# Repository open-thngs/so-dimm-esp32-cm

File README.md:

# SO-DIMM-ESP32-S2-CM

This is a ESP32-S2 based Compute Module to replace the Raspberry Pi's Compute Modules CM2 and CM3. This module is footprint compatible to the Raspberry Pi CM (SO-DIMM-DDR2). The ESP32-S2 brings USB, I2C and SPI.

Because the ESP32 is not running a Linux OS this module can not replace any CM in any project due to its limitations but it might helps others to reduce cost and resources needed to run the project. The ESP32-S2 consumes only 1/3 of the power the CM does. The ESP can also bring WiFi to your project if needed.

The Module also contains 2x GPIO-Expander which are used to be compatible with any GPIO of the Raspberry Pi Compute Module which gives you 48 GPIOs to be used in total.

Features:
- 2x I2C
- 2x SPI
- 1x UART
- USB

## OSHW Certified

[OSHW] DE000133 | Certified open source hardware | oshwa.org/cert

[https://certification.oshwa.org/de000133.html](https://certification.oshwa.org/de000133.html)

## GPIO Reference

GPIO Expander references E1_IOX_Y = < Expander >_< Bank >_< GPIO >
Example: E1_IO0_2 is the GPIO 2 of the Bank 0 in GPIO Expander 1. GPIO count starts at 0.

GPIO Expander E1 has address 0x20
GPIO Expander E2 has address 0x21

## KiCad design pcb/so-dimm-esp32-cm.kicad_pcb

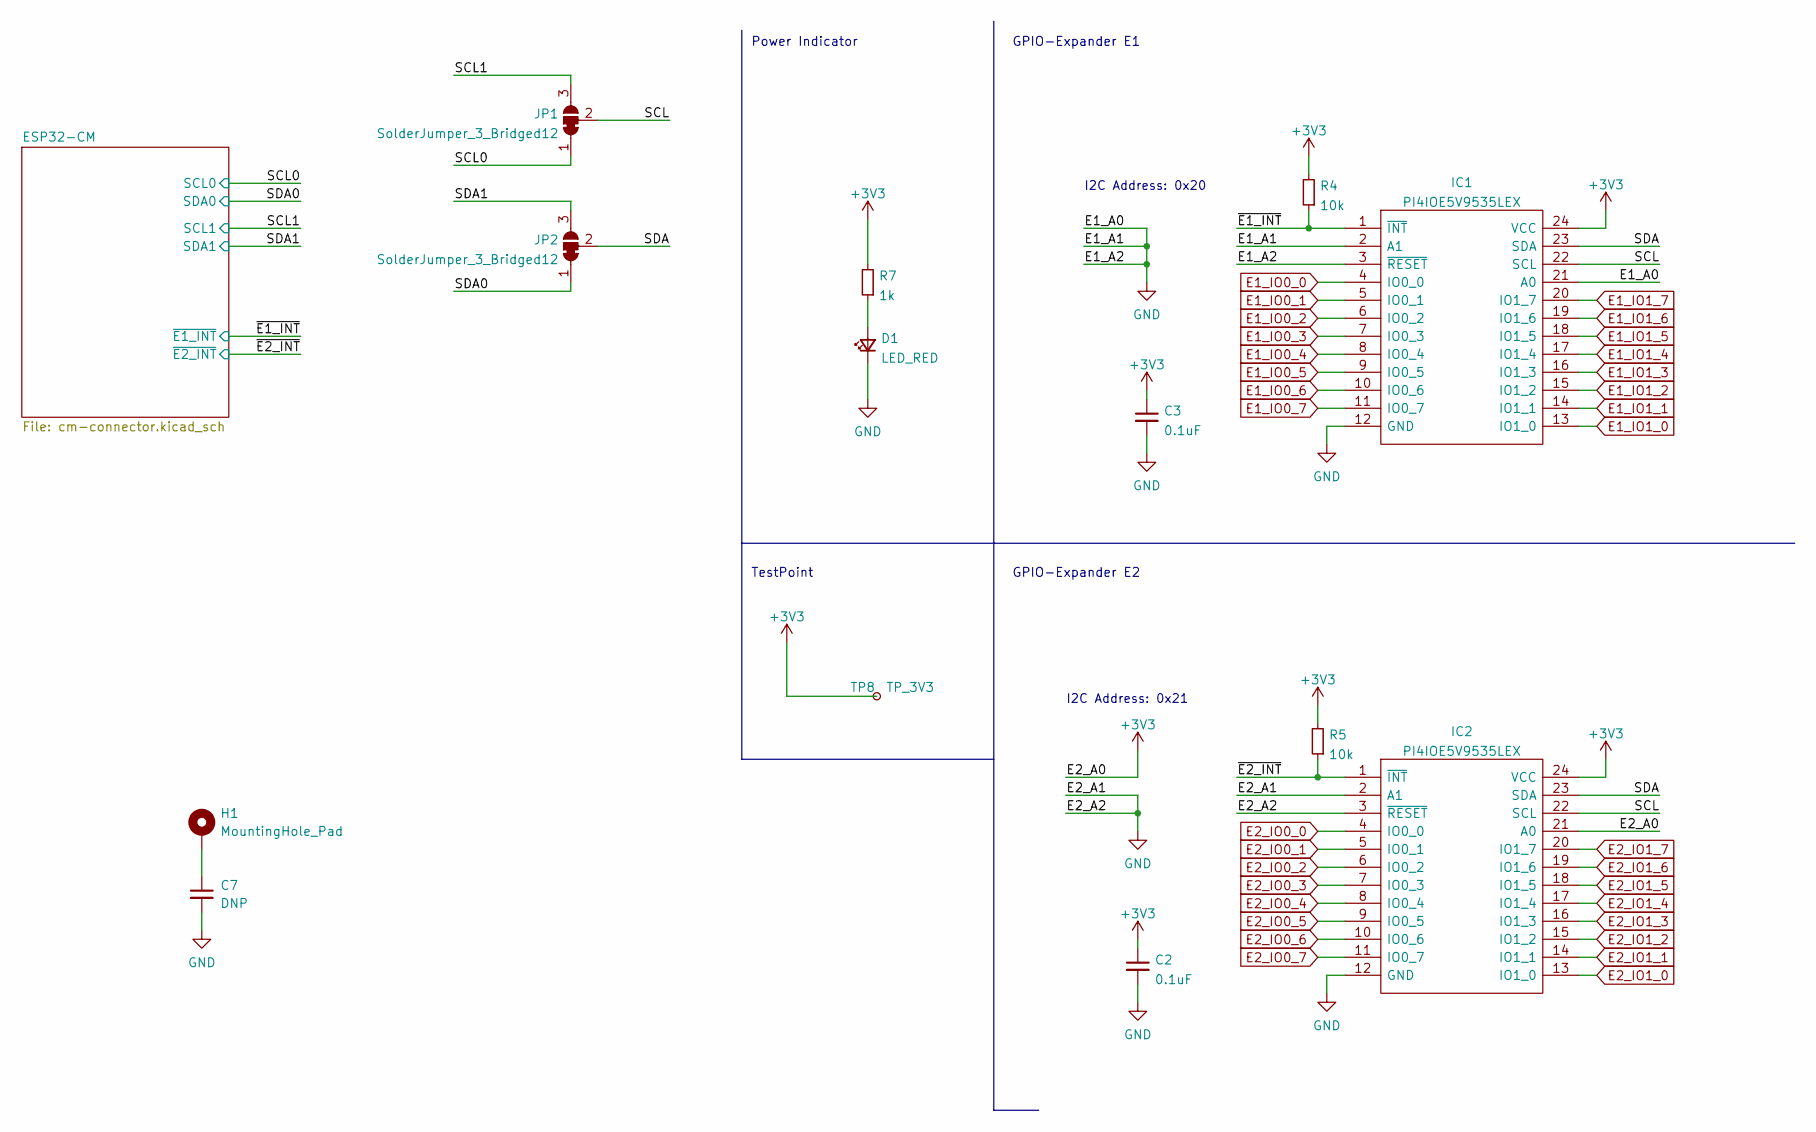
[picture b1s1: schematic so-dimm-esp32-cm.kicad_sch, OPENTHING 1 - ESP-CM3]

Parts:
C2, C3: 0.1uF; C_0603_1608Metric
C7: DNP; C_0603_1608Metric
D1: LED_RED; LED_0603_1608Metric
H1: MountingHole_Pad; MountingHole_2.7mm_Pad_Via
IC1, IC2: PI4IOE5V9535LEX; SOP65P640X120-24N; Manufacturer_Part_Number PI4IOE5V9535LEX; Mouser Part Number 729-PI4IOE5V9535LEX
JP1, JP2: SolderJumper_3_Bridged12; SolderJumper-3_P1.3mm_Bridged12_RoundedPad1.0x1.5mm
R4, R5: 10k; R_0603_1608Metric
R7: 1k; R_0603_1608Metric
TP8: TP_3V3; TestPoint_Pad_D1.0mm

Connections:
+3V3: C2.1, C3.1, IC1.24 (VCC), IC2.21 (A0), IC2.24 (VCC), R4.2, R5.2, R7.2, TP8.1; also elsewhere on the board
/SCL: IC1.22 (SCL), IC2.22 (SCL), JP1.2 (C)
/SCL0: JP1.1 (A); also elsewhere on the board
/SCL1: JP1.3 (B); also elsewhere on the board
/SDA: IC1.23 (SDA), IC2.23 (SDA), JP2.2 (C)
/SDA0: JP2.1 (A); also elsewhere on the board
/SDA1: JP2.3 (B); also elsewhere on the board
/~E1_INT: IC1.1 (~INT), R4.1; also elsewhere on the board
/~E2_INT: IC2.1 (~INT), R5.1; also elsewhere on the board
E1_IO0_0: IC1.4 (IO0_0); also elsewhere on the board
E1_IO0_1: IC1.5 (IO0_1); also elsewhere on the board
E1_IO0_2: IC1.6 (IO0_2); also elsewhere on the board
E1_IO0_3: IC1.7 (IO0_3); also elsewhere on the board
E1_IO0_4: IC1.8 (IO0_4); also elsewhere on the board
E1_IO0_5: IC1.9 (IO0_5); also elsewhere on the board
E1_IO0_6: IC1.10 (IO0_6); also elsewhere on the board
E1_IO0_7: IC1.11 (IO0_7); also elsewhere on the board
E1_IO1_0: IC1.13 (IO1_0); also elsewhere on the board
E1_IO1_1: IC1.14 (IO1_1); also elsewhere on the board
E1_IO1_2: IC1.15 (IO1_2); also elsewhere on the board
E1_IO1_3: IC1.16 (IO1_3); also elsewhere on the board
E1_IO1_4: IC1.17 (IO1_4); also elsewhere on the board
E1_IO1_5: IC1.18 (IO1_5); also elsewhere on the board
E1_IO1_6: IC1.19 (IO1_6); also elsewhere on the board
E1_IO1_7: IC1.20 (IO1_7); also elsewhere on the board
E2_IO0_0: IC2.4 (IO0_0); also elsewhere on the board
E2_IO0_1: IC2.5 (IO0_1); also elsewhere on the board
E2_IO0_2: IC2.6 (IO0_2); also elsewhere on the board
E2_IO0_3: IC2.7 (IO0_3); also elsewhere on the board
E2_IO0_4: IC2.8 (IO0_4); also elsewhere on the board
E2_IO0_5: IC2.9 (IO0_5); also elsewhere on the board
E2_IO0_6: IC2.10 (IO0_6); also elsewhere on the board
E2_IO0_7: IC2.11 (IO0_7); also elsewhere on the board
E2_IO1_0: IC2.13 (IO1_0); also elsewhere on the board
E2_IO1_1: IC2.14 (IO1_1); also elsewhere on the board
E2_IO1_2: IC2.15 (IO1_2); also elsewhere on the board
E2_IO1_3: IC2.16 (IO1_3); also elsewhere on the board
E2_IO1_4: IC2.17 (IO1_4); also elsewhere on the board
E2_IO1_5: IC2.18 (IO1_5); also elsewhere on the board
E2_IO1_6: IC2.19 (IO1_6); also elsewhere on the board
E2_IO1_7: IC2.20 (IO1_7); also elsewhere on the board
GND: C2.2, C3.2, C7.2, D1.1 (K), IC1.2 (A1), IC1.3 (~RESET), IC1.12 (GND), IC1.21 (A0), IC2.2 (A1), IC2.3 (~RESET), IC2.12 (GND); also elsewhere on the board
unnamed: C7.1, H1.1
unnamed: D1.2 (A), R7.1

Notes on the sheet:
I2C Address: 0x20
GPIO-Expander E1
TestPoint
I2C Address: 0x21
Power Indicator
GPIO-Expander E2

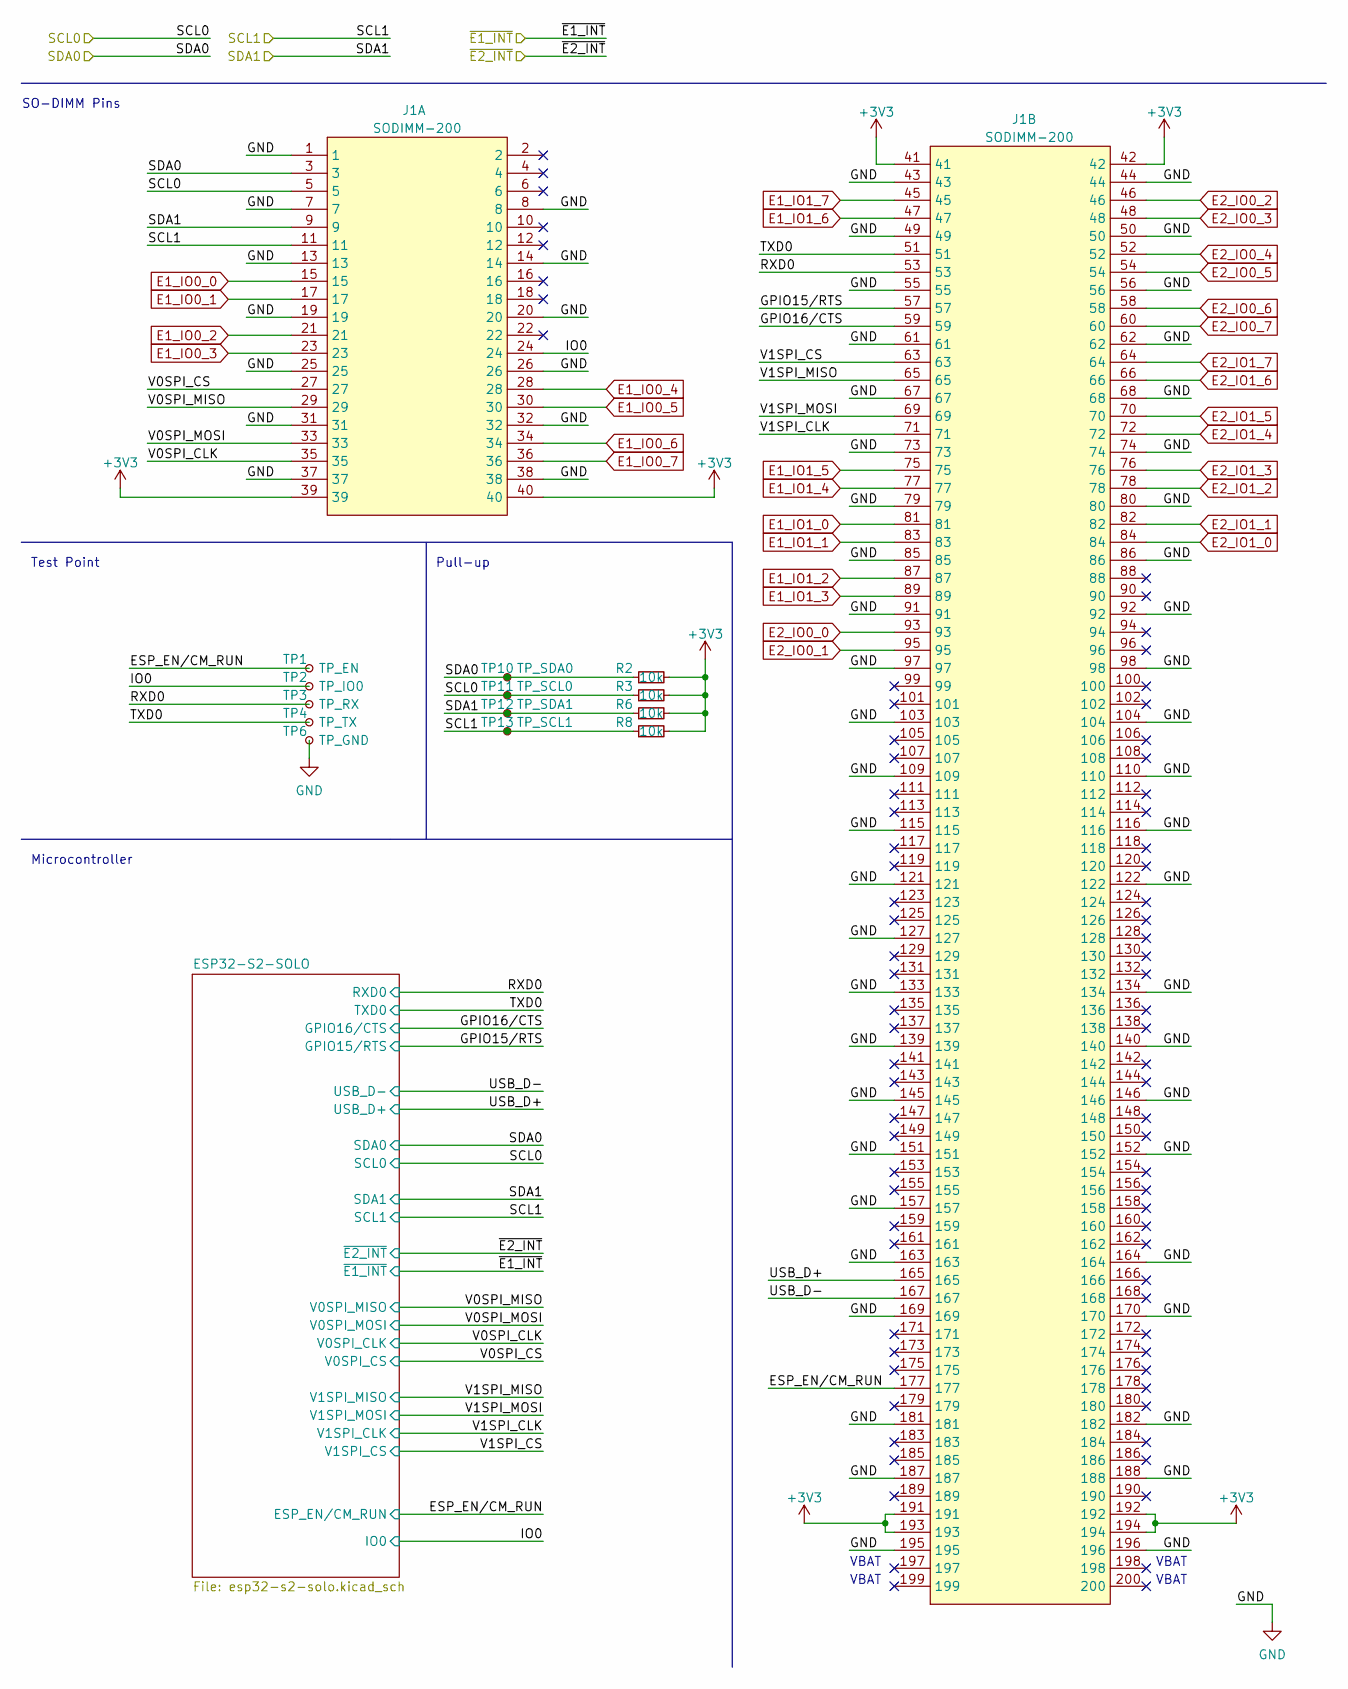
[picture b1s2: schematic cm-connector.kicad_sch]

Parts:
J1: SODIMM-200; SODIMM_DDR2_EDGE
R2, R3, R6, R8: 10k; R_0603_1608Metric
TP1: TP_EN; TestPoint_Pad_D1.0mm
TP2: TP_IO0; TestPoint_Pad_D1.0mm
TP3: TP_RX; TestPoint_Pad_D1.0mm
TP4: TP_TX; TestPoint_Pad_D1.0mm
TP6: TP_GND; TestPoint_Pad_D1.0mm
TP10: TP_SDA0; TestPoint_Pad_D1.0mm
TP11: TP_SCL0; TestPoint_Pad_D1.0mm
TP12: TP_SDA1; TestPoint_Pad_D1.0mm
TP13: TP_SCL1; TestPoint_Pad_D1.0mm

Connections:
+3V3: J1.39, J1.40, J1.41, J1.42, J1.191, J1.192, J1.193, J1.194, R2.2, R3.2, R6.2, R8.2; also elsewhere on the board
/ESP32-CM/ESP_EN/CM_RUN: J1.177, TP1.1; also elsewhere on the board
/ESP32-CM/GPIO15/RTS: J1.57; also elsewhere on the board
/ESP32-CM/GPIO16/CTS: J1.59; also elsewhere on the board
/ESP32-CM/IO0: J1.24, TP2.1; also elsewhere on the board
/ESP32-CM/RXD0: J1.53, TP3.1; also elsewhere on the board
/ESP32-CM/TXD0: J1.51, TP4.1; also elsewhere on the board
/ESP32-CM/USB_D+: J1.165; also elsewhere on the board
/ESP32-CM/USB_D-: J1.167; also elsewhere on the board
/ESP32-CM/V0SPI_CLK: J1.35; also elsewhere on the board
/ESP32-CM/V0SPI_CS: J1.27; also elsewhere on the board
/ESP32-CM/V0SPI_MISO: J1.29; also elsewhere on the board
/ESP32-CM/V0SPI_MOSI: J1.33; also elsewhere on the board
/ESP32-CM/V1SPI_CLK: J1.71; also elsewhere on the board
/ESP32-CM/V1SPI_CS: J1.63; also elsewhere on the board
/ESP32-CM/V1SPI_MISO: J1.65; also elsewhere on the board
/ESP32-CM/V1SPI_MOSI: J1.69; also elsewhere on the board
/SCL0: J1.5, R3.1, TP11.1; also elsewhere on the board
/SCL1: J1.11, R8.1, TP13.1; also elsewhere on the board
/SDA0: J1.3, R2.1, TP10.1; also elsewhere on the board
/SDA1: J1.9, R6.1, TP12.1; also elsewhere on the board
E1_IO0_0: J1.15; also elsewhere on the board
E1_IO0_1: J1.17; also elsewhere on the board
E1_IO0_2: J1.21; also elsewhere on the board
E1_IO0_3: J1.23; also elsewhere on the board
E1_IO0_4: J1.28; also elsewhere on the board
E1_IO0_5: J1.30; also elsewhere on the board
E1_IO0_6: J1.34; also elsewhere on the board
E1_IO0_7: J1.36; also elsewhere on the board
E1_IO1_0: J1.81; also elsewhere on the board
E1_IO1_1: J1.83; also elsewhere on the board
E1_IO1_2: J1.87; also elsewhere on the board
E1_IO1_3: J1.89; also elsewhere on the board
E1_IO1_4: J1.77; also elsewhere on the board
E1_IO1_5: J1.75; also elsewhere on the board
E1_IO1_6: J1.47; also elsewhere on the board
E1_IO1_7: J1.45; also elsewhere on the board
E2_IO0_0: J1.93; also elsewhere on the board
E2_IO0_1: J1.95; also elsewhere on the board
E2_IO0_2: J1.46; also elsewhere on the board
E2_IO0_3: J1.48; also elsewhere on the board
E2_IO0_4: J1.52; also elsewhere on the board
E2_IO0_5: J1.54; also elsewhere on the board
E2_IO0_6: J1.58; also elsewhere on the board
E2_IO0_7: J1.60; also elsewhere on the board
E2_IO1_0: J1.84; also elsewhere on the board
E2_IO1_1: J1.82; also elsewhere on the board
E2_IO1_2: J1.78; also elsewhere on the board
E2_IO1_3: J1.76; also elsewhere on the board
E2_IO1_4: J1.72; also elsewhere on the board
E2_IO1_5: J1.70; also elsewhere on the board
E2_IO1_6: J1.66; also elsewhere on the board
E2_IO1_7: J1.64; also elsewhere on the board
GND: J1.1, J1.7, J1.8, J1.13, J1.14, J1.19, J1.20, J1.25, J1.26, J1.31, J1.32, J1.37, J1.38, J1.43, J1.44, J1.49, J1.50, J1.55, J1.56, J1.61, J1.62, J1.67, J1.68, J1.73, J1.74, J1.79, J1.80, J1.85, J1.86, J1.91, J1.92, J1.97, J1.98, J1.103, J1.104, J1.109, J1.110, J1.115, J1.116, J1.121, J1.122, J1.127, J1.133, J1.134, J1.139, J1.140, J1.145, J1.146, J1.151, J1.152, J1.157, J1.163, J1.164, J1.169, J1.170, J1.181, J1.182, J1.187, J1.188, J1.195, J1.196, TP6.1; also elsewhere on the board

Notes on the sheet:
Microcontroller
SO-DIMM Pins
VBAT
Pull-up
Test Point

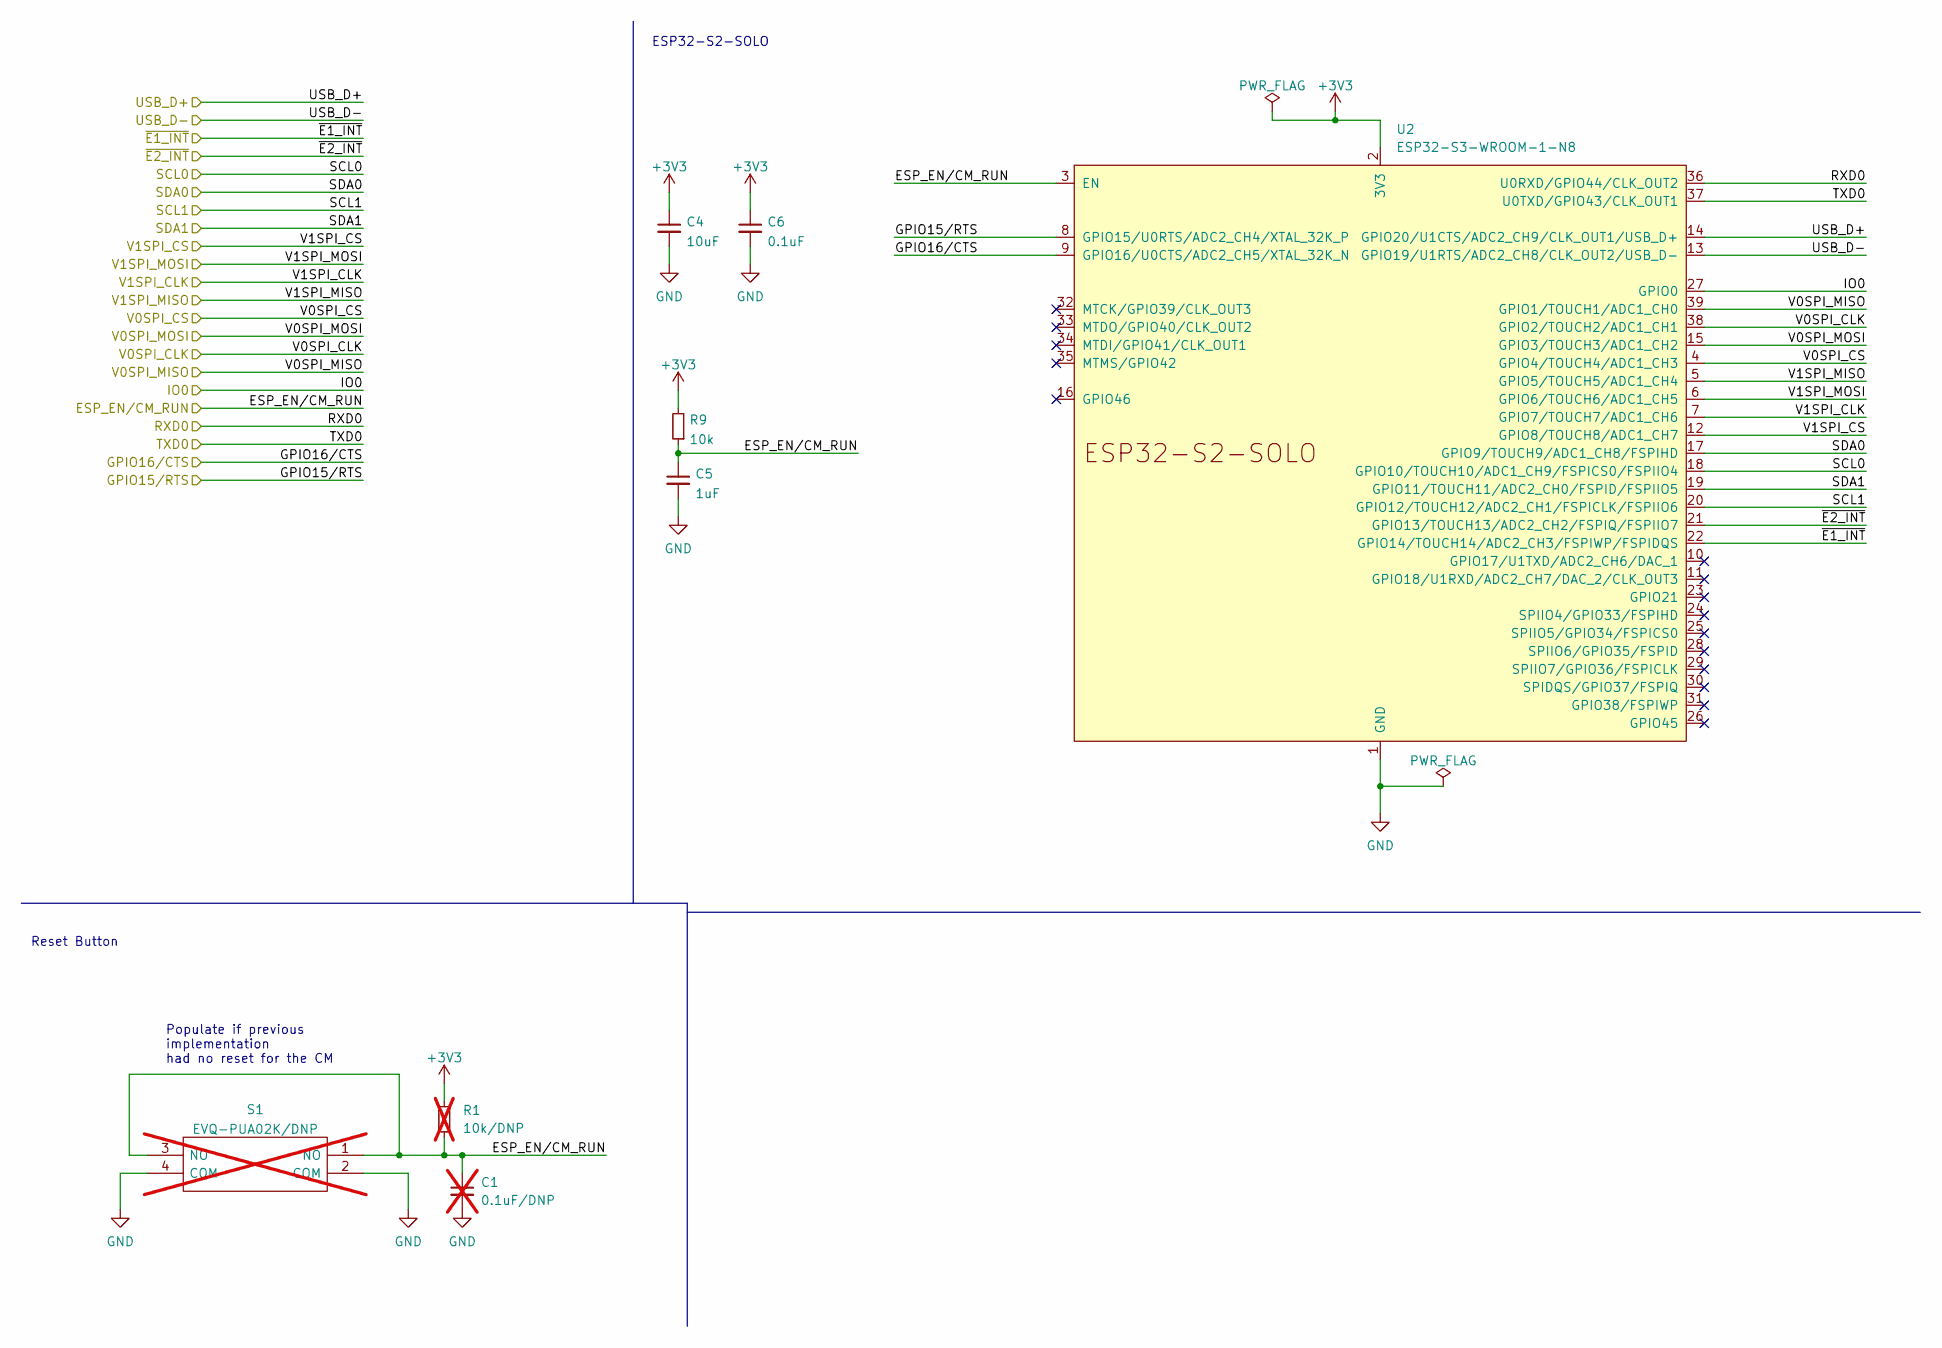
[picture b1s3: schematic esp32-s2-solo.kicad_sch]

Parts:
C1: 0.1uF/DNP; C_0603_1608Metric; not fitted
C4: 10uF; C_0603_1608Metric
C5: 1uF; C_0603_1608Metric
C6: 0.1uF; C_0603_1608Metric
R1: 10k/DNP; R_0603_1608Metric; not fitted
R9: 10k; R_0603_1608Metric
S1: EVQ-PUA02K/DNP; EVQPUA02K; Manufacturer_Part_Number EVQ-PUA02K; Mouser Part Number 667-EVQ-PUA02K; not fitted
U2: ESP32-S3-WROOM-1-N8; ESP32-S2-SOLO

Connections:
+3V3: C4.1, C6.1, R1.2, R9.2, U2.2 (3V3); also elsewhere on the board
/ESP32-CM/ESP_EN/CM_RUN: C1.1, C5.1, R1.1, R9.1, S1.1 (NO), S1.3 (NO), U2.3 (EN); also elsewhere on the board
/ESP32-CM/GPIO15/RTS: U2.8 (GPIO15/U0RTS/ADC2_CH4/XTAL_32K_P); also elsewhere on the board
/ESP32-CM/GPIO16/CTS: U2.9 (GPIO16/U0CTS/ADC2_CH5/XTAL_32K_N); also elsewhere on the board
/ESP32-CM/IO0: U2.27 (GPIO0); also elsewhere on the board
/ESP32-CM/RXD0: U2.36 (U0RXD/GPIO44/CLK_OUT2); also elsewhere on the board
/ESP32-CM/TXD0: U2.37 (U0TXD/GPIO43/CLK_OUT1); also elsewhere on the board
/ESP32-CM/USB_D+: U2.14 (GPIO20/U1CTS/ADC2_CH9/CLK_OUT1/USB_D+); also elsewhere on the board
/ESP32-CM/USB_D-: U2.13 (GPIO19/U1RTS/ADC2_CH8/CLK_OUT2/USB_D-); also elsewhere on the board
/ESP32-CM/V0SPI_CLK: U2.38 (GPIO2/TOUCH2/ADC1_CH1); also elsewhere on the board
/ESP32-CM/V0SPI_CS: U2.4 (GPIO4/TOUCH4/ADC1_CH3); also elsewhere on the board
/ESP32-CM/V0SPI_MISO: U2.39 (GPIO1/TOUCH1/ADC1_CH0); also elsewhere on the board
/ESP32-CM/V0SPI_MOSI: U2.15 (GPIO3/TOUCH3/ADC1_CH2); also elsewhere on the board
/ESP32-CM/V1SPI_CLK: U2.7 (GPIO7/TOUCH7/ADC1_CH6); also elsewhere on the board
/ESP32-CM/V1SPI_CS: U2.12 (GPIO8/TOUCH8/ADC1_CH7); also elsewhere on the board
/ESP32-CM/V1SPI_MISO: U2.5 (GPIO5/TOUCH5/ADC1_CH4); also elsewhere on the board
/ESP32-CM/V1SPI_MOSI: U2.6 (GPIO6/TOUCH6/ADC1_CH5); also elsewhere on the board
/SCL0: U2.18 (GPIO10/TOUCH10/ADC1_CH9/FSPICS0/FSPIIO4); also elsewhere on the board
/SCL1: U2.20 (GPIO12/TOUCH12/ADC2_CH1/FSPICLK/FSPIIO6); also elsewhere on the board
/SDA0: U2.17 (GPIO9/TOUCH9/ADC1_CH8/FSPIHD); also elsewhere on the board
/SDA1: U2.19 (GPIO11/TOUCH11/ADC2_CH0/FSPID/FSPIIO5); also elsewhere on the board
/~E1_INT: U2.22 (GPIO14/TOUCH14/ADC2_CH3/FSPIWP/FSPIDQS); also elsewhere on the board
/~E2_INT: U2.21 (GPIO13/TOUCH13/ADC2_CH2/FSPIQ/FSPIIO7); also elsewhere on the board
GND: C1.2, C4.2, C5.2, C6.2, S1.2 (COM), S1.4 (COM), U2.1 (GND), U2.40 (GND), U2.41 (GND); also elsewhere on the board

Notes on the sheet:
ESP32-S2-SOLO
Reset Button
Populate if previous implementation had no reset for the CM

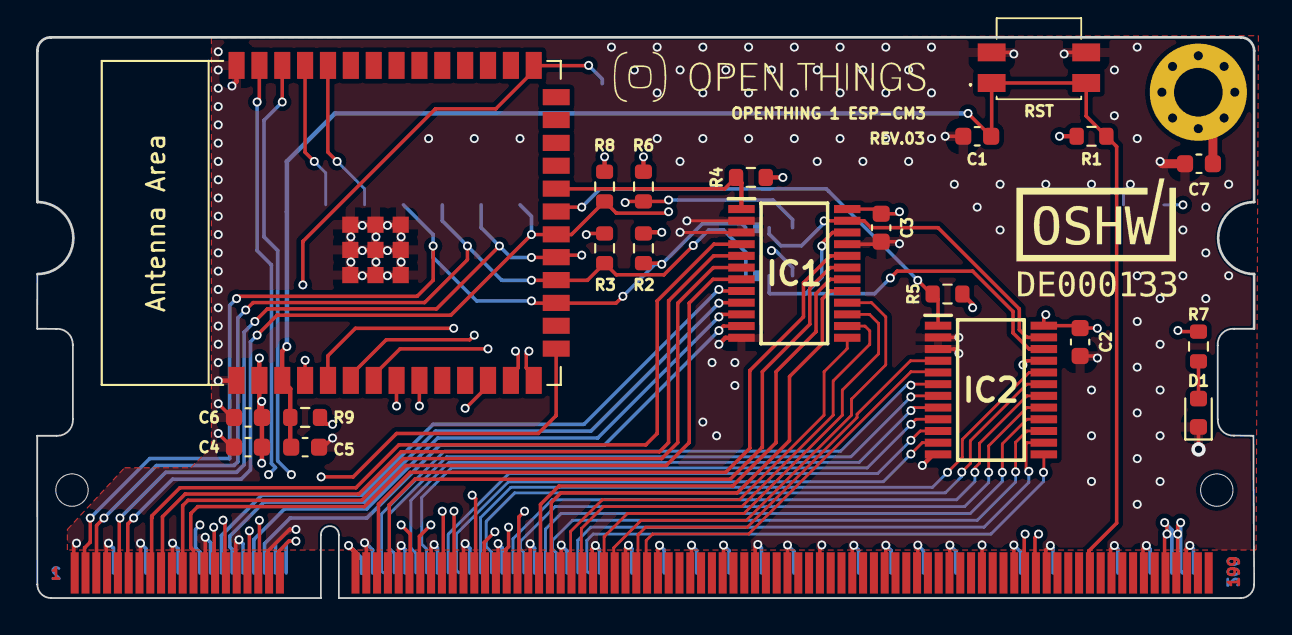
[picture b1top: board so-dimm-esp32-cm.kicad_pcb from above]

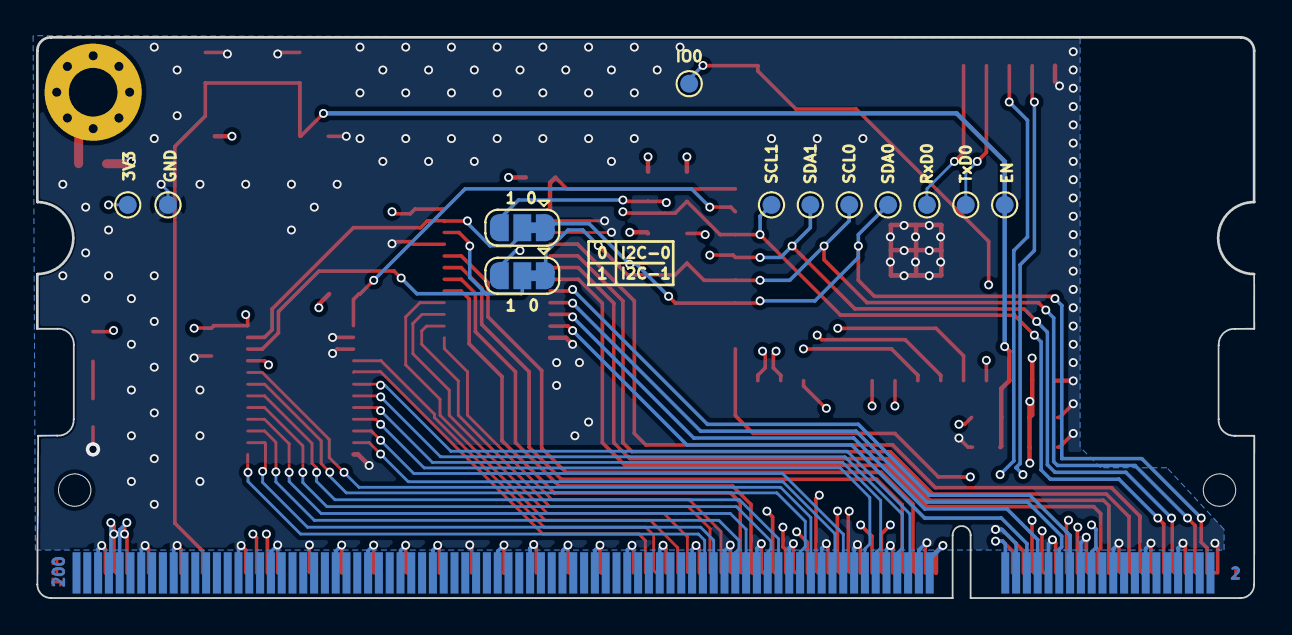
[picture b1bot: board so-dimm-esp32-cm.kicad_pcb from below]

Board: 4 copper layers, 67.6 x 31.1 mm, 37 parts (12 on the bottom side), 60 nets.

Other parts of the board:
G1, G2: LOGO

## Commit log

2022-10-22 initial commit REV0.1
2022-10-22 removed unused files
2022-10-22 Disable DRC and ERC for debugging
2022-10-22 Changed images for build process
2022-10-22 Reenable DRC and ERC
2022-10-22 Replaced README
2022-10-22 Switch version v2 to v2_k6
2022-10-22 reverse version switch
2022-10-22 set files explicitly
2022-10-22 fix ERC issues
2022-10-22 remove components from the BOM which are DNP
2022-10-22 remove components bom
2022-10-22 enable jlcpcb plot
2022-10-22 disabled jlcplot
2023-01-04 Added jumper to swap I2C-0 with I2C-1 for the GPIO-Expanders
    The GPIO expanders are using 0x20 and 0x21 as addresses and to avoid clashes with existing carrierboards I made the I2Cchannel switchable. Default is I2C-0 now
2023-01-04 Fix ERC warnings
2023-02-10 Added more information to README + gpio reference
2023-02-10 Added gpio-expander information
2023-02-10 Added feature Image to the README
2023-02-13 Added jpg img license information
2023-02-15 Added licenses information text file to the license folder
2023-02-25 Changed pinout reference table
2023-02-25 Added OSHW certificate ID image as SVG and PNG
2023-02-25 Added OSHW Certifcation information and OSHW facts to readme + added images of oshw facts
2023-02-25 Added OSHW ID Image with white background
2023-02-25 Test added markdown image size change using html tag
2023-02-25 Removed larger version of oshw id from readme
2023-02-25 Added lincense file for new images
2023-02-25 Renamed license information filename to fix failed build
2023-02-25 Moved the license information file to root due to failing github action REUSE
2023-02-25 Still try to fic the license issue for license information file wtf
2023-02-25 Add actual license information to the license file of the license-information file
2023-02-25 Moved the license-information files again due to failing build
2023-03-24 Refactored PCB Layer to have one dedicated GND Layer + rerouted traces + removed debug connector and added IO0 to the SO-DIMM connector + added decoupling caps and delay circuit for ESP32 module
2023-04-03 Convert to KiCad 7
2023-07-14 Add toit test code
2023-07-14 Add micropython test code
2023-07-14 Add toit entry classes
2023-07-14 Add arduino test code
2023-07-14 Generated BOM and schematics
2023-07-14 Add IMG of the board
2023-08-08 Applied KiBot Action for basic manufacturing data
2023-08-08 Fix file ending for config file
2023-08-11 Fix missing ESP-SOLO footprint and Symbol
2023-08-11 Add license file for image
2023-08-11 Moved ESP SOLO 3D File into project
2023-09-01 Added Via stitching and ground plane to top and bottom layers
2023-09-01 Changed camera angle for the 3D rendering
2023-09-01 Try to fix missing render png
2023-09-01 Update kibot.yml to use dev version of the container instead of latest
2023-09-01 Update kibot.yml moving back to latest kibot version
2023-09-02 Update esp-cm3.kibot.yaml to print PNG of the PCB
2023-09-02 add missing pages key
2023-09-02 Made pages a list instead of dict
2023-09-03 Changed from pcb_print to pcb draw
2023-09-08 Added inner layers to Gerber files for KiBot
2023-09-11 Added CE Sign + Moved footprint a tiny bit + added so-dimm numbering silk + increased revision number
2023-09-11 Added Datasheet config
2023-09-14 Added Datasheet of the ESP-CM3
2023-09-14 Removed fußnote from datasheet
2023-09-18 Fix SO-DIMM Pinout differences to DDR2 CM3 + Added ground drill
2023-09-21 Add panelisation edges
2023-09-21 Change positionfile export to be CSV files
2023-09-21 Add license information for datasheet pdf
2023-09-21 Renamed Datasheet and renamed license information file accordingly
2023-09-25 Added KiBot configs for PCBWay and JLCPCB
2023-09-25 Removed KiBot config for JLCPCB position
2023-09-25 Removed configs for KiBot again
2023-09-27 Finally fix SODIMM Pin layout based on datasheet of the 1612618 connector
2023-09-29 Set reset button to be DNP
2023-09-29 Removed mounting hole from BOM
2023-10-09 Change copper to edge clearance from 0.025 to 0.15
2024-03-20 Removed parts from BOM and applied clearence changes
2024-03-21 Ignored thermal-relief + changed ESP32-S2 to be ESP32-S3-N8
2024-03-21 Added assembly file + bom XLSX File (K&G)
2024-03-21 Added Generated production data
2024-11-06 Add some test classes for arduino code and toit
2024-11-06 Moved some silkscreen to user drawings
2024-11-06 add production data board dimensions and specification
